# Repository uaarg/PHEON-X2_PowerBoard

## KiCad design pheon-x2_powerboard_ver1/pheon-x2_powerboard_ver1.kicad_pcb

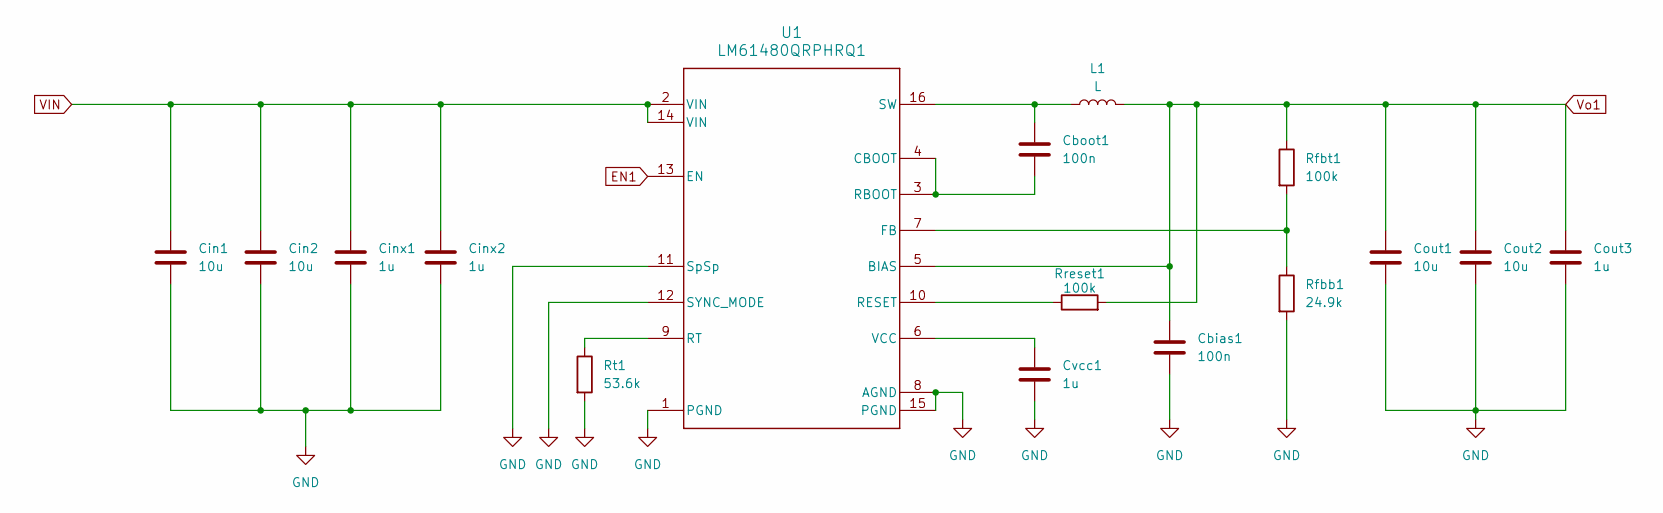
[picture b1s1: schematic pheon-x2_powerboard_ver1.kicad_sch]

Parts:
Cbias1: 100n; C_0402_1005Metric_Pad0.74x0.62mm_HandSolder
Cboot1: 100n; C_0402_1005Metric_Pad0.74x0.62mm_HandSolder
Cin1, Cin2: 10u; C_1210_3225Metric_Pad1.33x2.70mm_HandSolder
Cinx1, Cinx2: 1u; C_0603_1608Metric_Pad1.08x0.95mm_HandSolder
Cout1, Cout2: 10u; C_1206_3216Metric_Pad1.33x1.80mm_HandSolder
Cout3: 1u; C_1206_3216Metric_Pad1.33x1.80mm_HandSolder
Cvcc1: 1u; C_0603_1608Metric_Pad1.08x0.95mm_HandSolder
L1: L; WE-HCI_1365
Rfbb1: 24.9k; R_0603_1608Metric_Pad0.98x0.95mm_HandSolder
Rfbt1: 100k; R_0402_1005Metric_Pad0.72x0.64mm_HandSolder
Rreset1: 100k; R_0402_1005Metric_Pad0.72x0.64mm_HandSolder
Rt1: 53.6k; R_0402_1005Metric_Pad0.72x0.64mm_HandSolder
U1: LM61480QRPHRQ1; RPH0016A

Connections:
EN1: U1.13 (EN)
GND: Cbias1.2, Cin1.2, Cin2.2, Cinx1.2, Cinx2.2, Cout1.2, Cout2.2, Cout3.2, Cvcc1.2, Rfbb1.2, Rt1.2, U1.1 (PGND), U1.8 (AGND), U1.11 (SpSp), U1.12 (SYNC_MODE), U1.15 (PGND)
unnamed: Cboot1.2, U1.3 (RBOOT), U1.4 (CBOOT)
unnamed: Rfbb1.1, Rfbt1.2, U1.7 (FB)
unnamed: Rreset1.1, U1.10 (RESET)
unnamed: Rt1.1, U1.9 (RT)
unnamed: Cboot1.1, L1.1, U1.16 (SW)
unnamed: Cvcc1.1, U1.6 (VCC)
VIN: Cin1.1, Cin2.1, Cinx1.1, Cinx2.1, U1.2 (VIN), U1.14 (VIN)
Vo1: Cbias1.1, Cout1.1, Cout2.1, Cout3.1, L1.2, Rfbt1.1, Rreset1.2, U1.5 (BIAS)

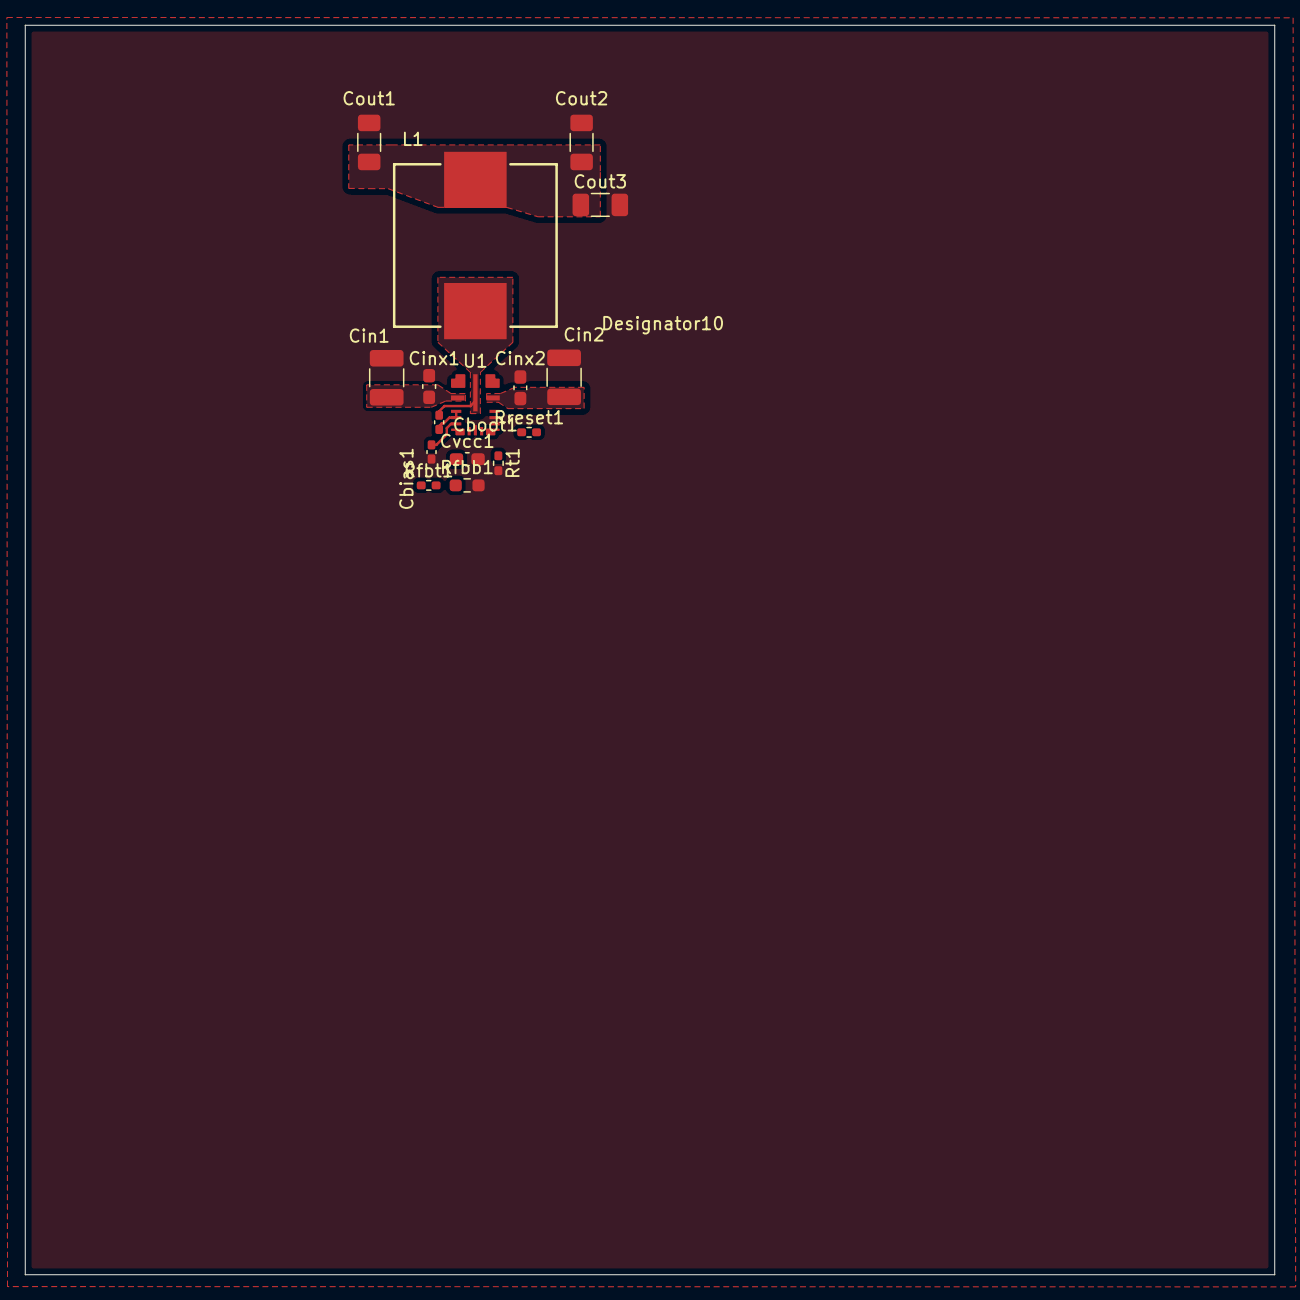
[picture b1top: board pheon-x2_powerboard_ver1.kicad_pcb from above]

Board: 4 copper layers, 100.0 x 100.0 mm, 16 parts (0 on the bottom side), 9 nets.

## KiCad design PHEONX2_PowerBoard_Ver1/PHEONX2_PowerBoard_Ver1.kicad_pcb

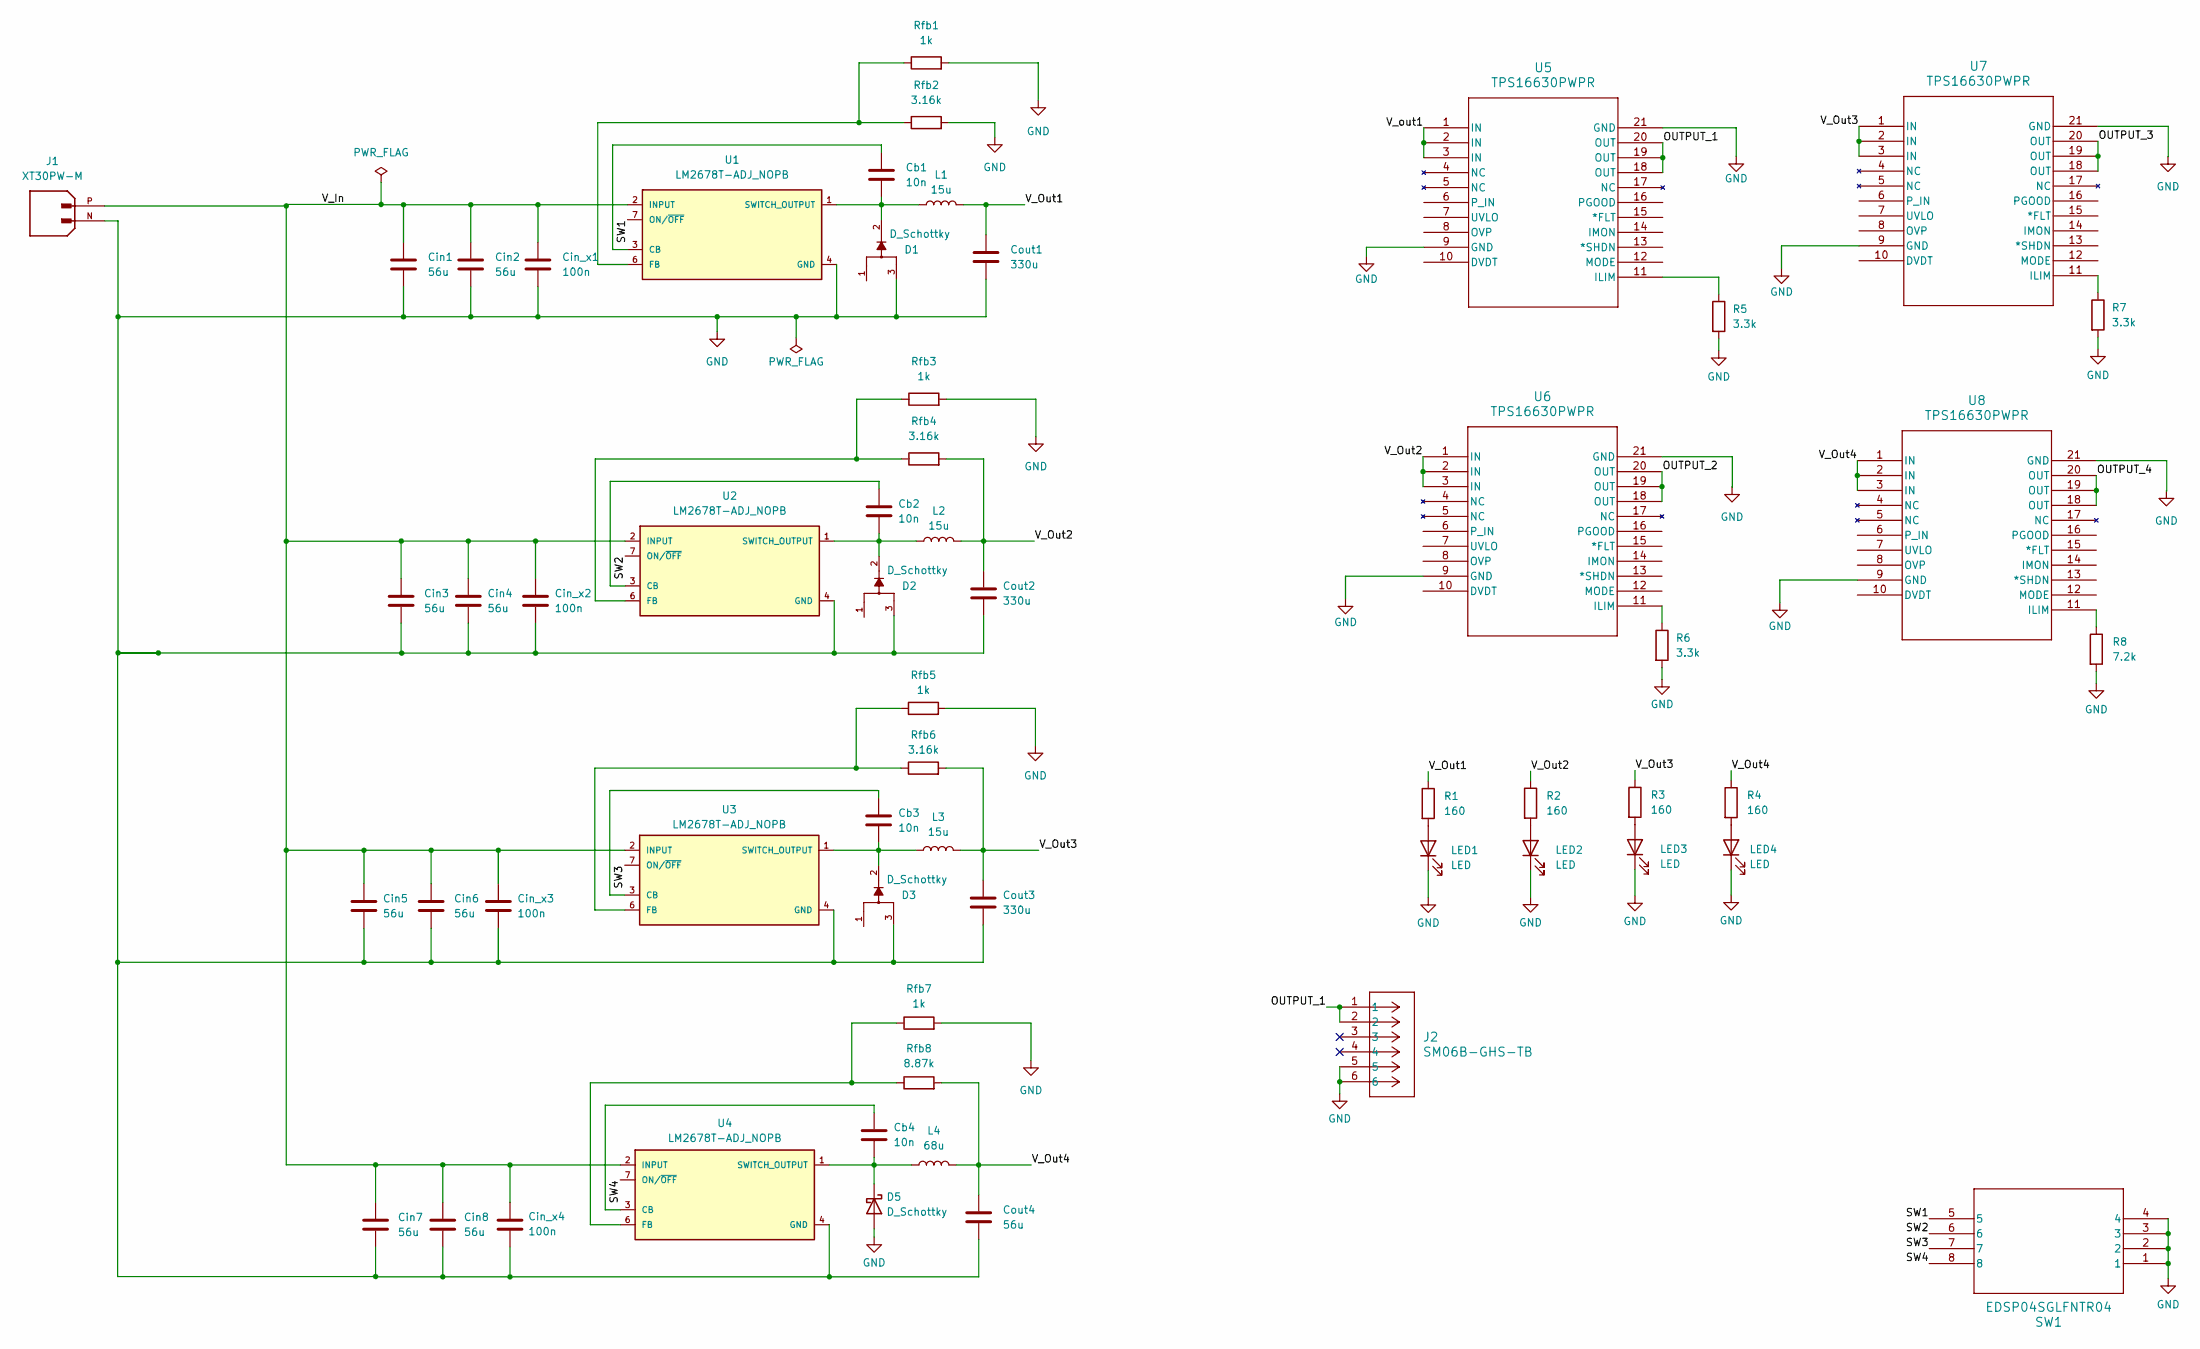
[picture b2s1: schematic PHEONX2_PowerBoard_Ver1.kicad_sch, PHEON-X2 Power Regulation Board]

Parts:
Cb1, Cb2, Cb3, Cb4: 10n; C_0805_2012Metric
Cin1, Cin2, Cin3, Cin4, Cin5, Cin6, Cin7, Cin8: 56u; CAP_EEHZA1J560P
Cin_x1, Cin_x2, Cin_x3, Cin_x4: 100n; C_0805_2012Metric
Cout1, Cout2, Cout3: 330u; CAP_10SVPC330M
Cout4: 56u; CP_Elec_6.3x5.4
D1, D2, D3: D_Schottky; DPAK228P1005X240-4N; PARTREV A
D5: D_Schottky; SK220ATR
J1: XT30PW-M; AMASS_XT30PW-M; PARTREV 1.2
J2: SM06B-GHS-TB
L1, L2, L3: 15u; IND_MSS1210-153MEB
L4: 68u; IND_MSS1210-153MEB
LED1, LED2, LED3, LED4: LED; LED_0805_2012Metric_Pad1.15x1.40mm_HandSolder
R1, R2, R3, R4: 160; R_0805_2012Metric_Pad1.20x1.40mm_HandSolder
R5, R6, R7: 3.3k; R_0805_2012Metric_Pad1.20x1.40mm_HandSolder
R8: 7.2k; R_0805_2012Metric_Pad1.20x1.40mm_HandSolder
Rfb1, Rfb3, Rfb5, Rfb7: 1k; R_0805_2012Metric_Pad1.20x1.40mm_HandSolder
Rfb2, Rfb4, Rfb6: 3.16k; R_0805_2012Metric_Pad1.20x1.40mm_HandSolder
Rfb8: 8.87k; R_0805_2012Metric_Pad1.20x1.40mm_HandSolder
SW1: EDSP04SGLFNTR04; SW4_EDSP04SGLFNTR04_TEC-M
U1, U2, U3, U4: LM2678T-ADJ_NOPB; TS7B
U5, U6, U7, U8: TPS16630PWPR; HTSSOP20_PWP_TEX

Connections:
/OUTPUT_1: J2.1, J2.2, U5.18 (OUT), U5.19 (OUT), U5.20 (OUT)
/OUTPUT_2: U6.18 (OUT), U6.19 (OUT), U6.20 (OUT)
/OUTPUT_3: U7.18 (OUT), U7.19 (OUT), U7.20 (OUT)
/OUTPUT_4: U8.18 (OUT), U8.19 (OUT), U8.20 (OUT)
/SW1: SW1.5, U1.7 (ON/~OFF)
/SW2: SW1.6, U2.7 (ON/~OFF)
/SW3: SW1.7, U3.7 (ON/~OFF)
/SW4: SW1.8, U4.7 (ON/~OFF)
/V_In: Cin1.1, Cin2.1, Cin3.1, Cin4.1, Cin5.1, Cin6.1, Cin7.1, Cin8.1, Cin_x1.1, Cin_x2.1, Cin_x3.1, Cin_x4.1, J1.P, U1.2 (INPUT), U2.2 (INPUT), U3.2 (INPUT), U4.2 (INPUT)
/V_Out1: Cout1.1, L1.2, R1.1
/V_Out2: Cout2.1, L2.2, R2.1, Rfb4.2, U6.1 (IN), U6.2 (IN), U6.3 (IN)
/V_Out3: Cout3.1, L3.2, R3.1, Rfb6.2, U7.1 (IN), U7.2 (IN), U7.3 (IN)
/V_Out4: Cout4.1, L4.2, R4.1, Rfb8.2, U8.1 (IN), U8.2 (IN), U8.3 (IN)
/V_out1: U5.1 (IN), U5.2 (IN), U5.3 (IN)
GND: Cin1.2, Cin2.2, Cin3.2, Cin4.2, Cin5.2, Cin6.2, Cin7.2, Cin8.2, Cin_x1.2, Cin_x2.2, Cin_x3.2, Cin_x4.2, Cout1.2, Cout2.2, Cout3.2, Cout4.2, D1.3, D2.3, D3.3, D5.2 (A), J1.N, J2.5, J2.6, LED1.1 (K), LED2.1 (K), LED3.1 (K), LED4.1 (K), R5.2, R6.2, R7.2, R8.2, Rfb1.2, Rfb2.2, Rfb3.2, Rfb5.2, Rfb7.2, SW1.1, SW1.2, SW1.3, SW1.4, U1.4 (GND), U2.4 (GND), U3.4 (GND), U4.4 (GND), U5.9 (GND), U5.21 (GND), U6.9 (GND), U6.21 (GND), U7.9 (GND), U7.21 (GND), U8.9 (GND), U8.21 (GND)
unnamed: Cb4.2, D5.1 (K), L4.1, U4.1 (SWITCH_OUTPUT)
unnamed: LED1.2 (A), R1.2
unnamed: LED2.2 (A), R2.2
unnamed: LED3.2 (A), R3.2
unnamed: LED4.2 (A), R4.2
unnamed: Cb1.1, U1.3 (CB)
unnamed: Rfb1.1, Rfb2.1, U1.6 (FB)
unnamed: Cb1.2, D1.2, L1.1, U1.1 (SWITCH_OUTPUT)
unnamed: Cb2.1, U2.3 (CB)
unnamed: Rfb3.1, Rfb4.1, U2.6 (FB)
unnamed: Cb2.2, D2.2, L2.1, U2.1 (SWITCH_OUTPUT)
unnamed: Cb3.1, U3.3 (CB)
unnamed: Rfb5.1, Rfb6.1, U3.6 (FB)
unnamed: Cb3.2, D3.2, L3.1, U3.1 (SWITCH_OUTPUT)
unnamed: Cb4.1, U4.3 (CB)
unnamed: Rfb7.1, Rfb8.1, U4.6 (FB)
unnamed: R5.1, U5.11 (ILIM)
unnamed: R6.1, U6.11 (ILIM)
unnamed: R7.1, U7.11 (ILIM)
unnamed: R8.1, U8.11 (ILIM)

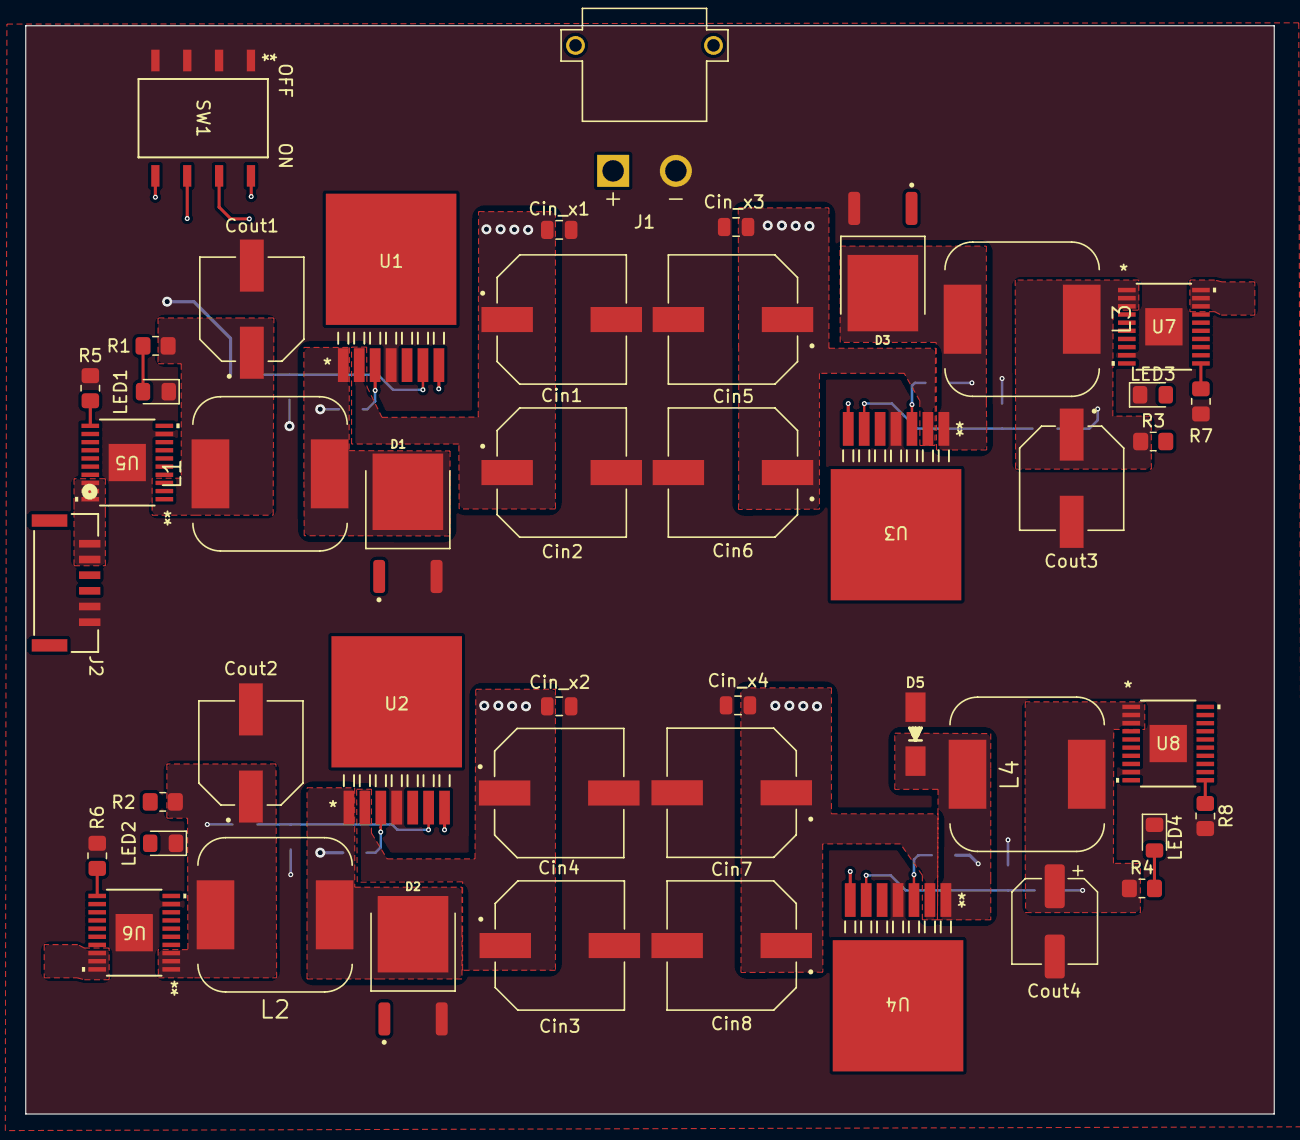
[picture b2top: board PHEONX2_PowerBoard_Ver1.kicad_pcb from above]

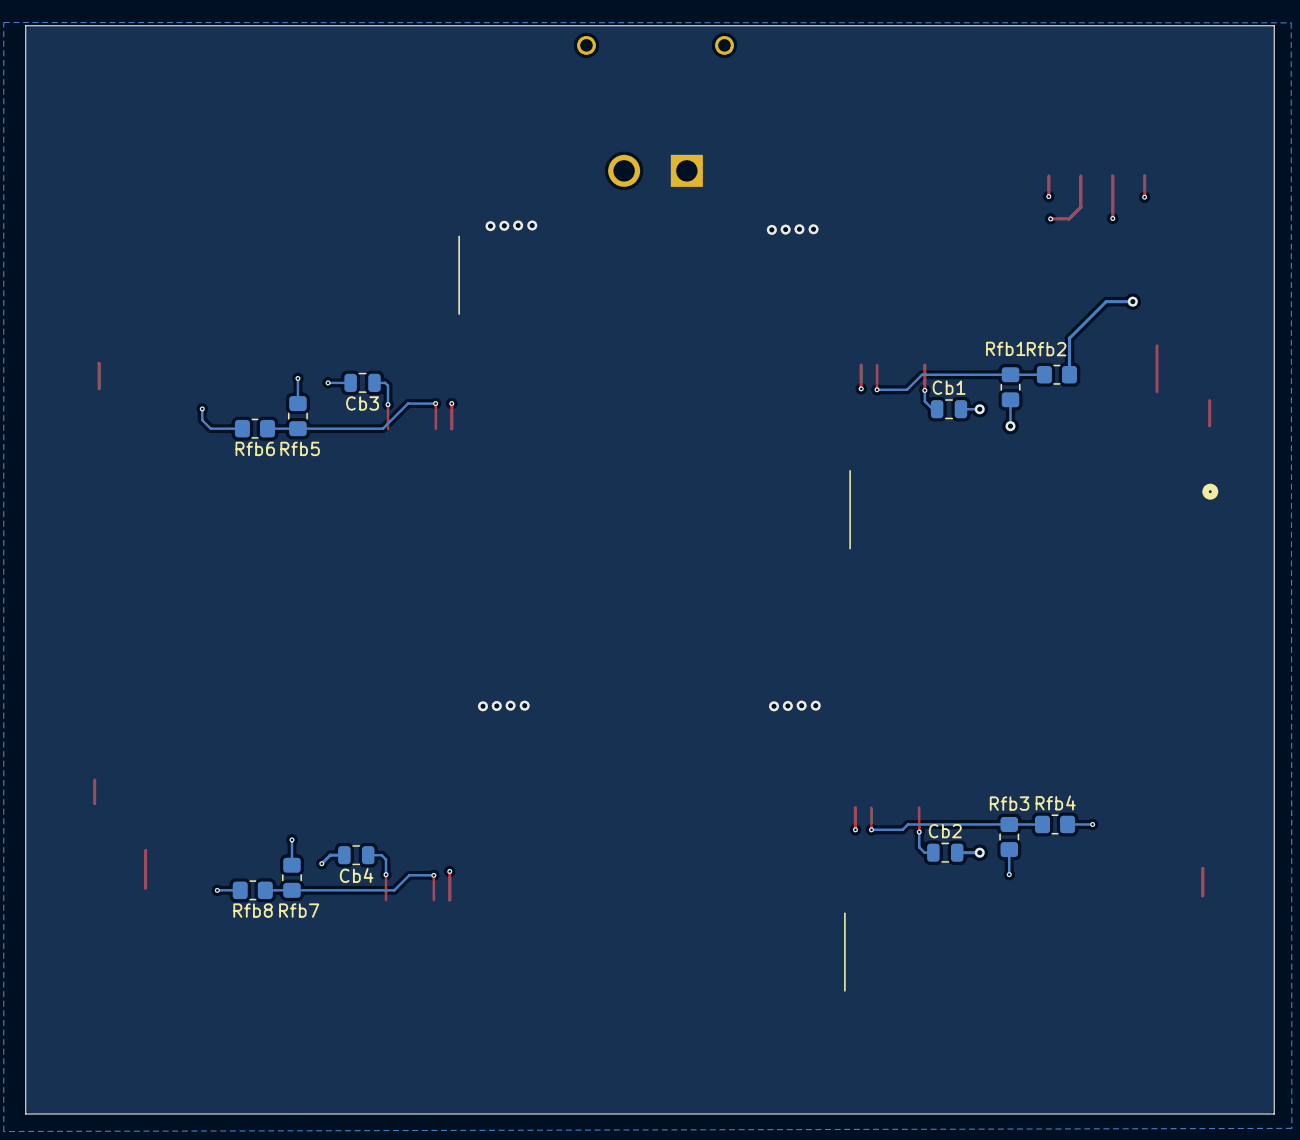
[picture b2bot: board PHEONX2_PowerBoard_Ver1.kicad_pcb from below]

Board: 4 copper layers, 99.5 x 86.8 mm, 59 parts (12 on the bottom side), 35 nets.
